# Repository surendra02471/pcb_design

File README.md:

Integrating the ESP32-WROOM-32D with the MPU-6050 opens up numerous possibilities in IoT, particularly in motion tracking and monitoring applications. This combination leverages the processing power and connectivity of the ESP32 with the sensing capabilities of the MPU-6050, enabling innovative solutions for health monitoring, robotics, gaming, and more.

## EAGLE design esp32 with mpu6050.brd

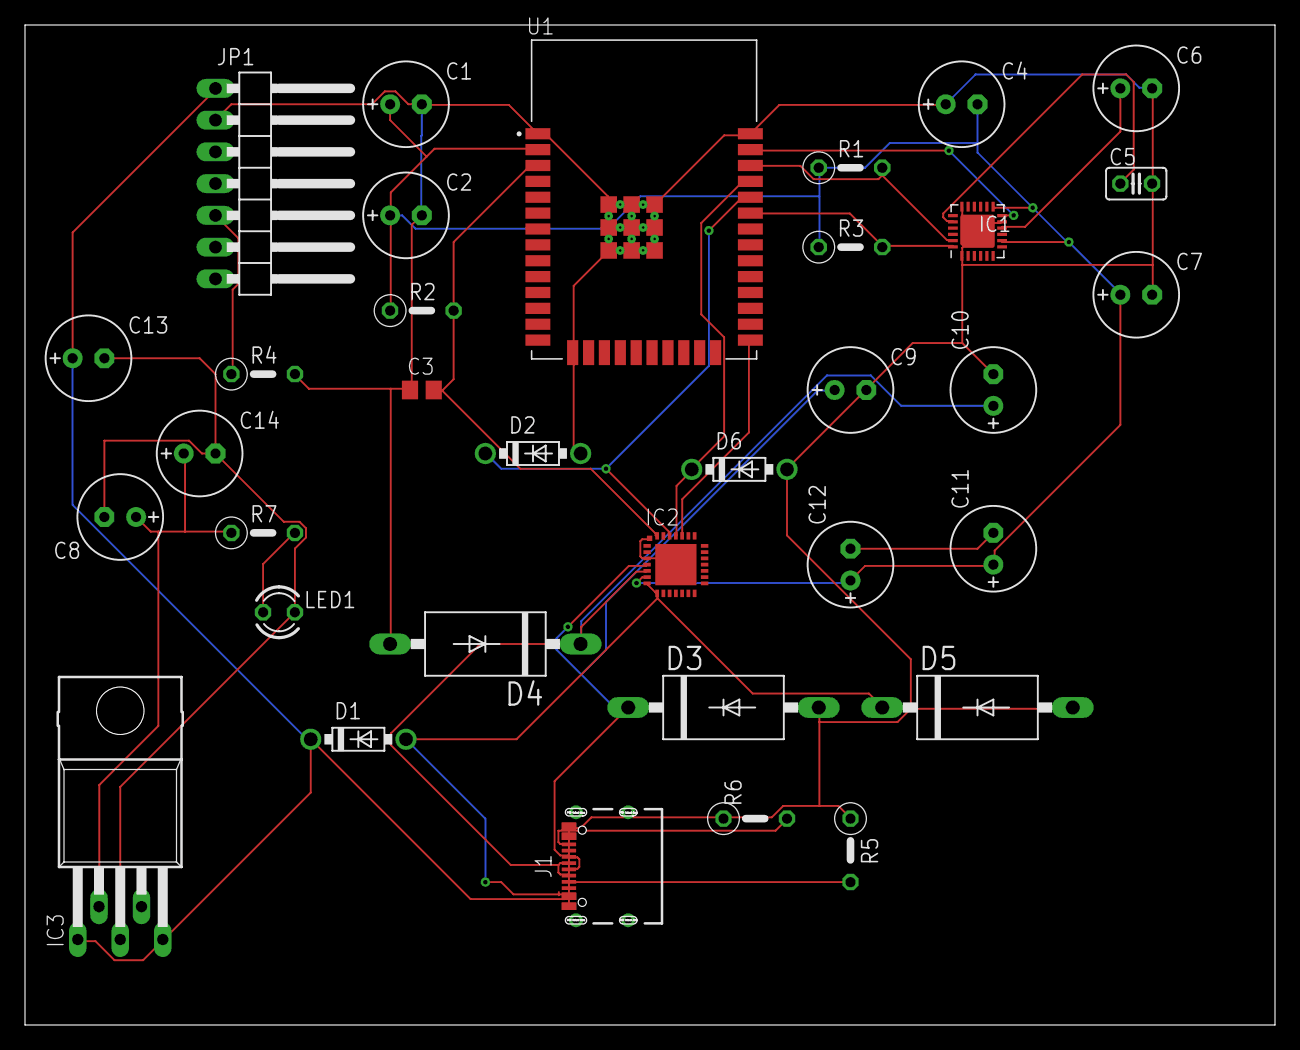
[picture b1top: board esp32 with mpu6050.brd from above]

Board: 2 copper layers, 100.0 x 80.0 mm, 34 parts (0 on the bottom side), 23 nets.

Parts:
C1: 0.1uf; E2,5-7
C2: 10uf; E2,5-7
C3: TBD; C0805
C4: 0.01u; E2,5-7
C5: 2200pf; C025-025X050
C6, C7, C8: 0.1u; E2,5-7
C9, C10, C11, C12: E2,5-7
C13: 4.7u; E2,5-7
C14: 10u; E2,5-7
D1, D2, D6: 1N5817-B; DO41-7.6
D3, D4, D5: ZZY22; P3-15
IC1: MPU6050; QFN50P400X400X95-25T265X275N
IC2: CP2101; MLP28
IC3: 3.3V; TO220-52
J1: 629722000214
JP1: 1X07/90
LED1: LED3MM
R1, R3: 4.7k; 0207/5V
R2: TBD; 0207/5V
R4, R5, R6, R7: 0207/5V
U1: ESP32-WROOM-32D; MODULE_ESP32-WROOM-32D

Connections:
0: C8.-, C13.-, C14.-, IC3.3, LED1.K
0V: C1.-, C2.-, C3.1, C4.+, C5.2, C6.-, C7.-, C9.-, C10.-, D2.A, D3.A, D4.A, D5.A, D6.A, IC1.1, IC1.11, IC1.18, IC1.25, J1.A1, J1.A12, J1.B1, J1.B12, JP1.2, R4.2, R5.1, R6.1, U1.1, U1.15, U1.38, U1.39_1, U1.39_2, U1.39_3, U1.39_4, U1.39_5, U1.39_6, U1.39_7, U1.39_8, U1.39_9, U1.39_10, U1.39_11, U1.39_12, U1.39_13, U1.39_14, U1.39_15, U1.39_16, U1.39_17, U1.39_18, U1.39_19, U1.39_20, U1.39_21
+3V3: C1.+, C2.+, C4.-, C7.+, C11.+, C12.+, IC1.8, IC1.13, IC2.6, R1.1, R2.1, R3.1, U1.2
+5V: C13.+, D1.C, IC3.1, IC3.5, J1.A4, JP1.1
AD0: JP1.5, R4.1
D(+): C9.+, D3.C, IC2.4, J1.A6, J1.B6
D(-): C10.+, D4.C, IC2.5, J1.A7, J1.B7
GND: C11.-, C12.-
unnamed: IC1.24, R3.2, U1.33
unnamed: C3.2, IC2.28, R2.2, U1.3
unnamed: C5.1, IC1.20
unnamed: LED1.A, R7.2
unnamed: C6.+, IC1.10
unnamed: IC1.23, R1.2, U1.36
unnamed: IC1.12, U1.37
unnamed: IC2.24, U1.25
unnamed: J1.B5, R6.2
unnamed: J1.A5, R5.2
unnamed: D1.A, D5.C, IC2.7, IC2.8, J1.B9
unnamed: D2.C, IC2.26, U1.34
unnamed: D6.C, IC2.25, U1.35
unnamed: IC2.3, IC2.EXP, IC2.M
unnamed: C8.+, C14.+, IC3.2, R7.1

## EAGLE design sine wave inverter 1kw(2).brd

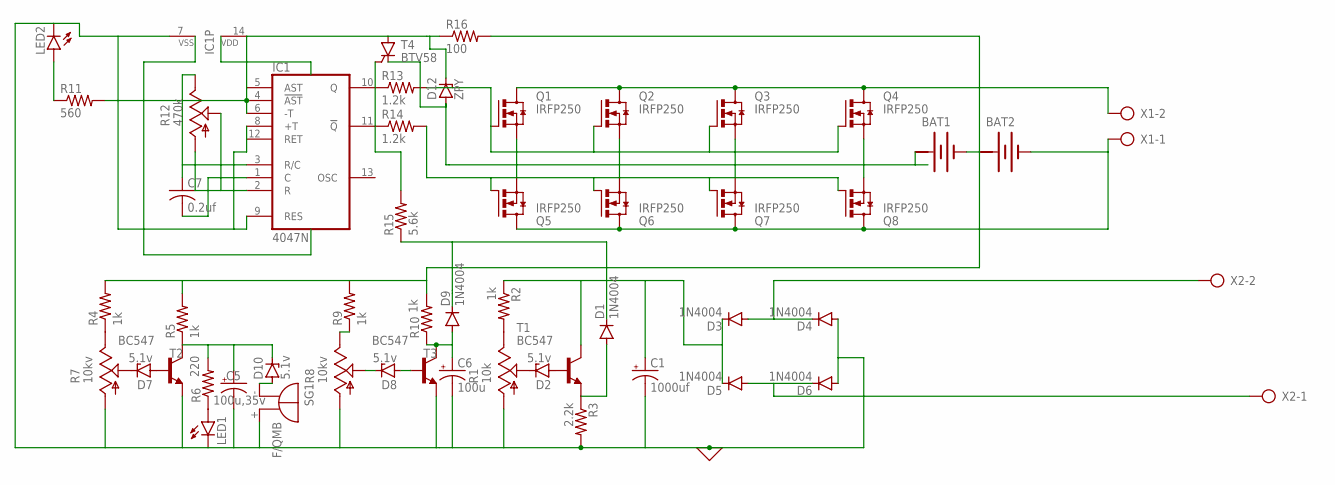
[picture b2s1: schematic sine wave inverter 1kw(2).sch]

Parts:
BAT1, BAT2: BATTERY
C1: 1000uf; E3,5-10
C5: 100u,35v; E3,5-10
C6: 100u; E3,5-10
C7: 0.2uf; C025-024X044
D1, D3, D4, D5, D6, D9: 1N4004; DO41-10
D2, D7, D8, D10: 5.1v; TO236
D12: ZPY; DO41Z10
IC1: 4047N; DIL14
LED1, LED2: LED5MM
Q1, Q2, Q3, Q4, Q5, Q6, Q7, Q8: IRFP250; TO-247AD-V
R1: 10k; B25P
R2, R4, R5, R9, R10: 1k; M1206
R3: 2.2k; M1206
R6: 220; M1206
R7, R8: 10kv; B25P
R11: 560; M1206
R12: 470k; B25P
R13, R14: 1.2k; M1206
R15: 5.6k; M1206
R16: 100; M1206
SG1: F/QMB
T1, T2, T3: BC547; TO92
T4: BTV58; TO220CS
X1, X2: AK300/2

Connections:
0: C1.-, C5.-, C6.-, D4.A, D6.A, IC1.7 (VSS), IC1.8 (+T), IC1.9 (RES), IC1.12 (RET), LED1.K (C), LED2.K (C), R1.A, R3.2, R7.A, R8.A, SG1.+ (-), T2.1 (E), T3.1 (E)
+: BAT1.+@1 (+), BAT2.+@1 (+)
unnamed: D2.C, R1.S
unnamed: R1.E, R2.2
unnamed: D2.A, T1.2 (B)
unnamed: D1.A, R3.1, T1.1 (E)
unnamed: C1.+, D3.C, D5.C, R2.1, T1.3 (C)
unnamed: BAT1.-, BAT2.+, R4.2, R5.2, R9.2, R10.2, R16.2
unnamed: Q1.G, Q2.G, Q3.G, Q4.G, R13.2
unnamed: D3.A, D4.C, X2.2
unnamed: Q1.S, Q5.S
unnamed: D5.A, D6.C, X2.1
unnamed: D7.C, R7.S
unnamed: Q2.S, Q6.S
unnamed: Q3.S, Q7.S
unnamed: Q4.S, Q8.S
unnamed: Q5.G, Q6.G, Q7.G, Q8.G, R14.2
unnamed: BAT2.-, Q5.D, Q6.D, Q7.D, Q8.D, X1.1
unnamed: Q1.D, Q2.D, Q3.D, Q4.D, X1.2
unnamed: D7.A, T2.2 (B)
unnamed: BAT1.+, D12.A, T4.C
unnamed: C5.+, D10.C, R5.1, R6.2, T2.3 (C)
unnamed: R4.1, R7.E
unnamed: LED1.A, R6.1
unnamed: D1.C, D9.C, R15.1
unnamed: R8.E, R9.1
unnamed: D8.C, R8.S
unnamed: D8.A, T3.2 (B)
unnamed: C6.+, D9.A, R10.1, T3.3 (C)
unnamed: D10.A, SG1.- (+)
unnamed: C7.2, IC1.1 (C)
unnamed: IC1.2 (R), R12.A, R12.S
unnamed: C7.1, IC1.3 (R/C), R12.E
unnamed: D12.C, IC1.4 (!AST), IC1.5 (AST), IC1.6 (-T), IC1.14 (VDD), R11.2, R16.1, T4.A
unnamed: IC1.10 (Q), R13.1
unnamed: IC1.11 (!Q), R14.1
unnamed: LED2.A, R11.1
unnamed: R15.2, T4.G

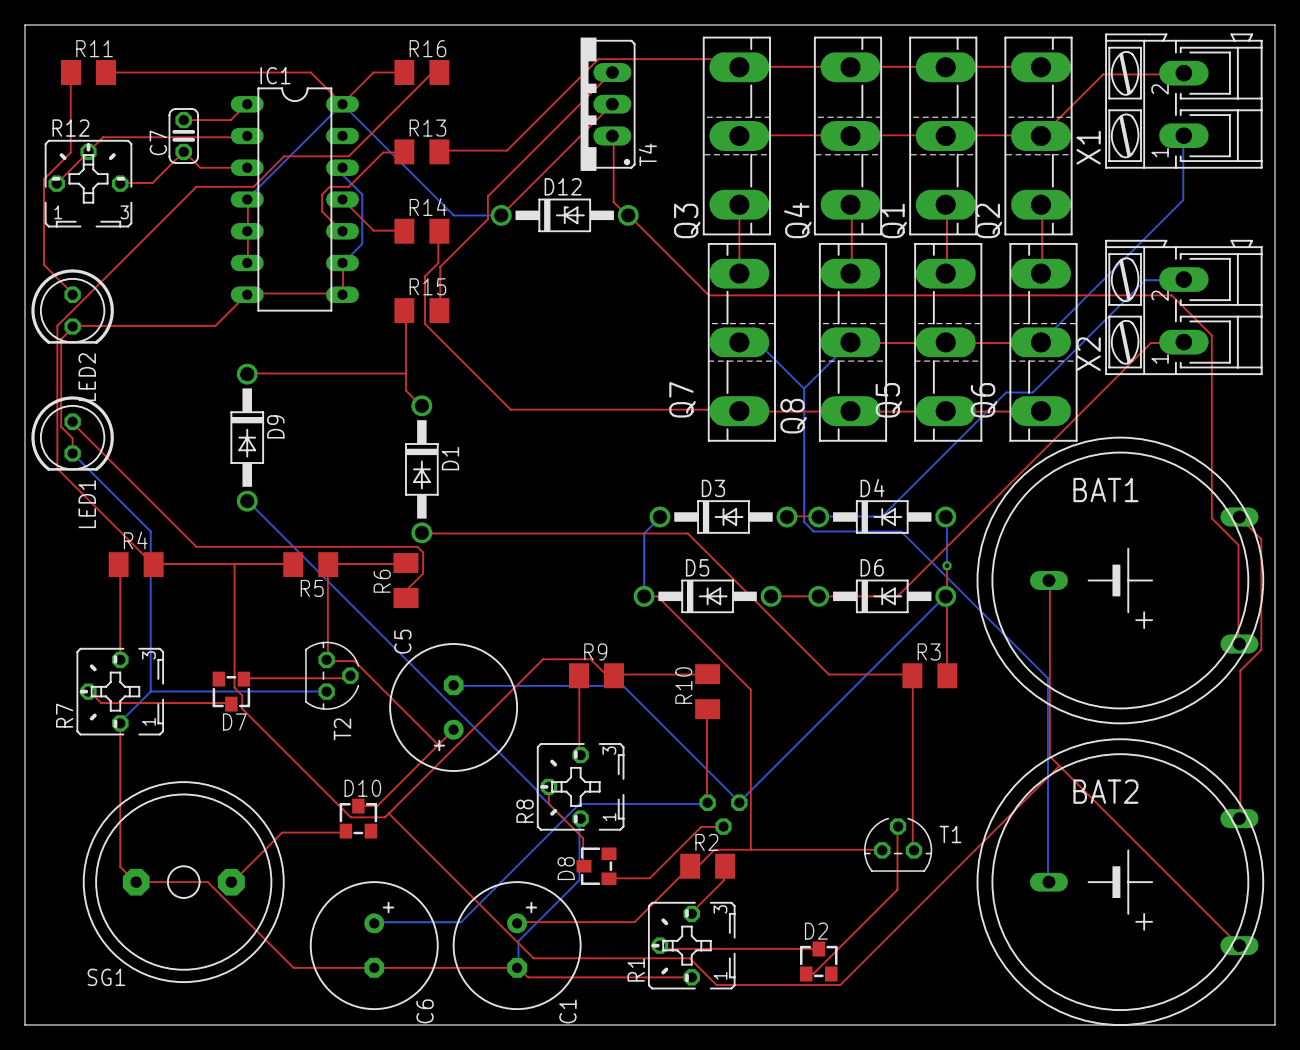
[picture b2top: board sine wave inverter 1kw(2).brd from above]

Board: 2 copper layers, 100.0 x 80.0 mm, 51 parts (1 on the bottom side), 38 nets.

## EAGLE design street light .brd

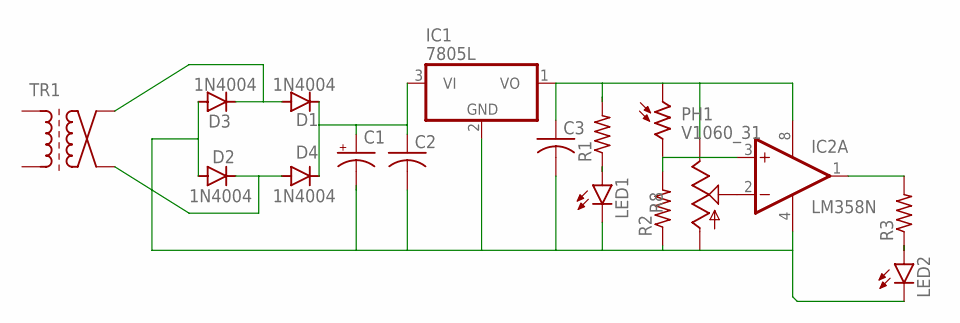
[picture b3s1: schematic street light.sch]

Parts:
C1: CPOL-USE3.5-10; E3,5-10
C2, C3: C-US025-024X044; C025-024X044
D1, D2, D3, D4: 1N4004; DO41-10
IC1: 7805L; TO92
IC2: LM358N; DIL08
LED1, LED2: LED5MM
PH1: V1060_31; TO-5_V10
R1, R2, R3: R-US_0207/10; 0207/10
R8: TRIM_US-CA6V; CA6V
TR1: MS35B

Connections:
unnamed: LED1.A, R1.1
unnamed: D1.A, D3.C, TR1.E2
unnamed: C3.1, IC1.1 (VO), IC2.8 (V+), PH1.1, R1.2, R8.E
unnamed: D2.C, D4.A, TR1.A2
unnamed: C1.-, C2.2, C3.2, D2.A, D3.A, IC1.2 (GND), IC2.4 (V-), LED1.K (C), LED2.K (C), R2.1, R8.A
unnamed: C1.+, C2.1, D1.C, D4.C, IC1.3 (VI)
unnamed: IC2.3 (+IN), PH1.2, R2.2
unnamed: LED2.A, R3.1
unnamed: IC2.2 (-IN), R8.S
unnamed: IC2.1 (OUT), R3.2

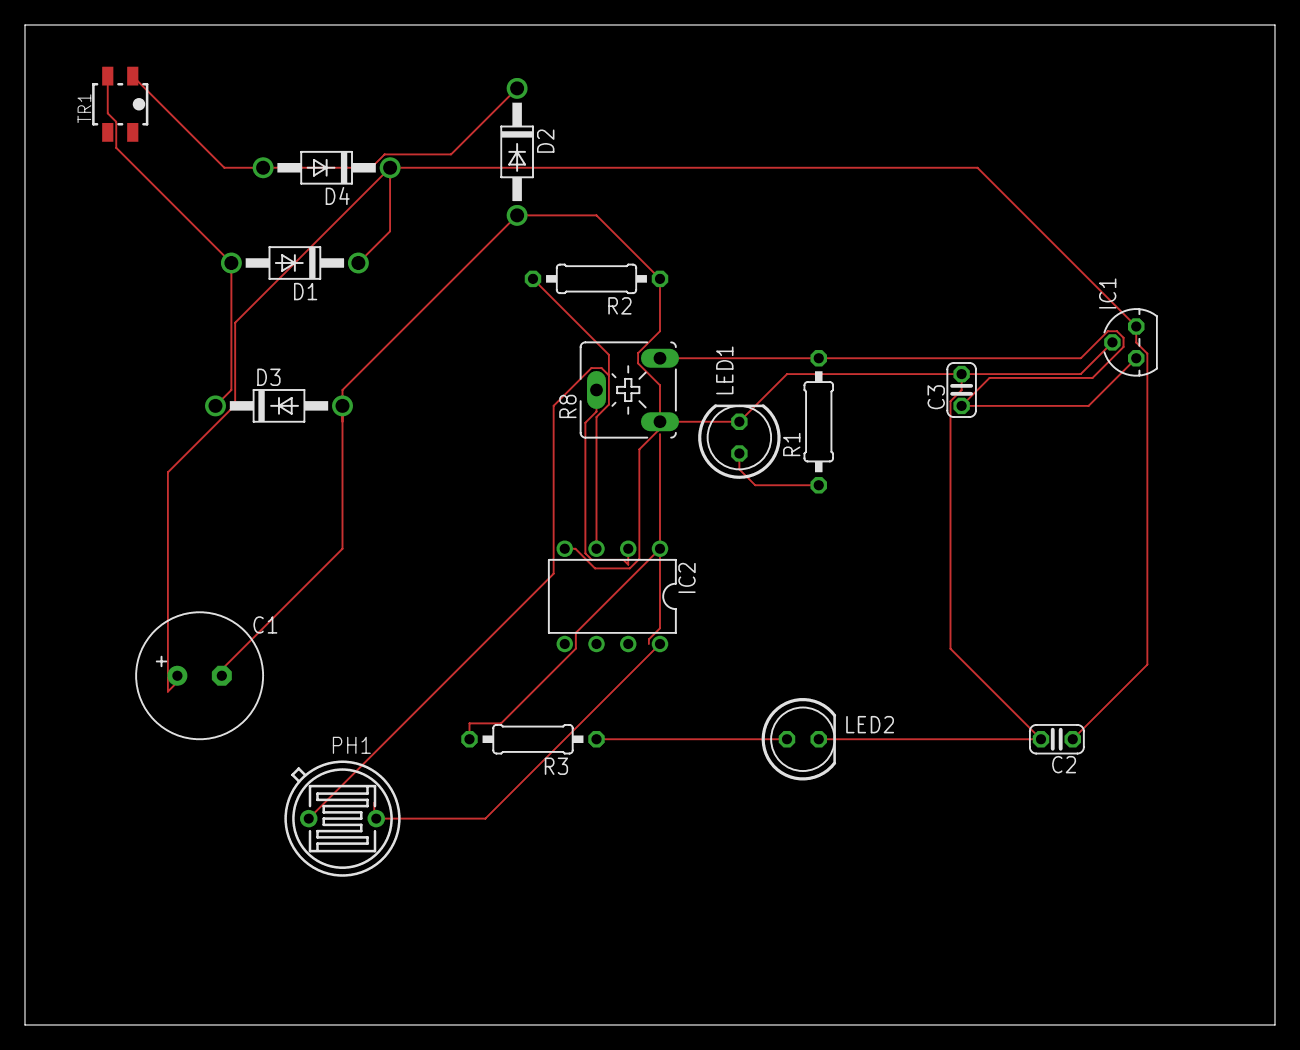
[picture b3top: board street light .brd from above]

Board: 2 copper layers, 100.0 x 80.0 mm, 17 parts (0 on the bottom side), 10 nets.

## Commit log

2024-08-31 Add files via upload
    Board design
2024-08-31 README.md
2024-10-03 Add files via upload
    Integrating the ESP32-WROOM-32D with the MPU-6050 opens up numerous possibilities in IoT, particularly in motion tracking and monitoring applications. This combination leverages the processing power 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

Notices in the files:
parts and their libraries:
Eagle_WR-USB: Copyright: Würth Elektronik
